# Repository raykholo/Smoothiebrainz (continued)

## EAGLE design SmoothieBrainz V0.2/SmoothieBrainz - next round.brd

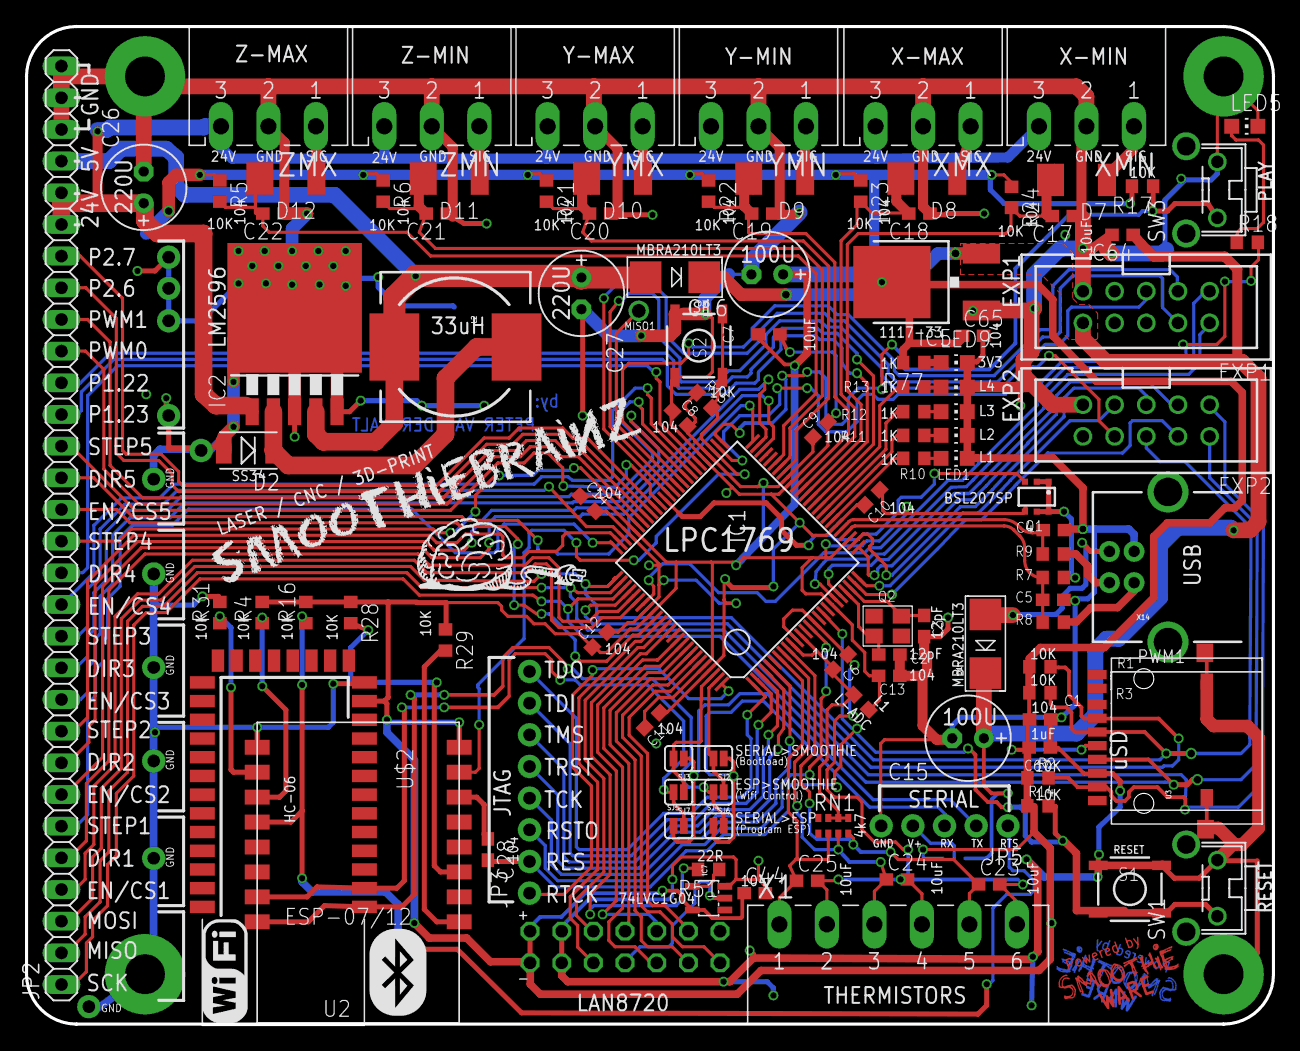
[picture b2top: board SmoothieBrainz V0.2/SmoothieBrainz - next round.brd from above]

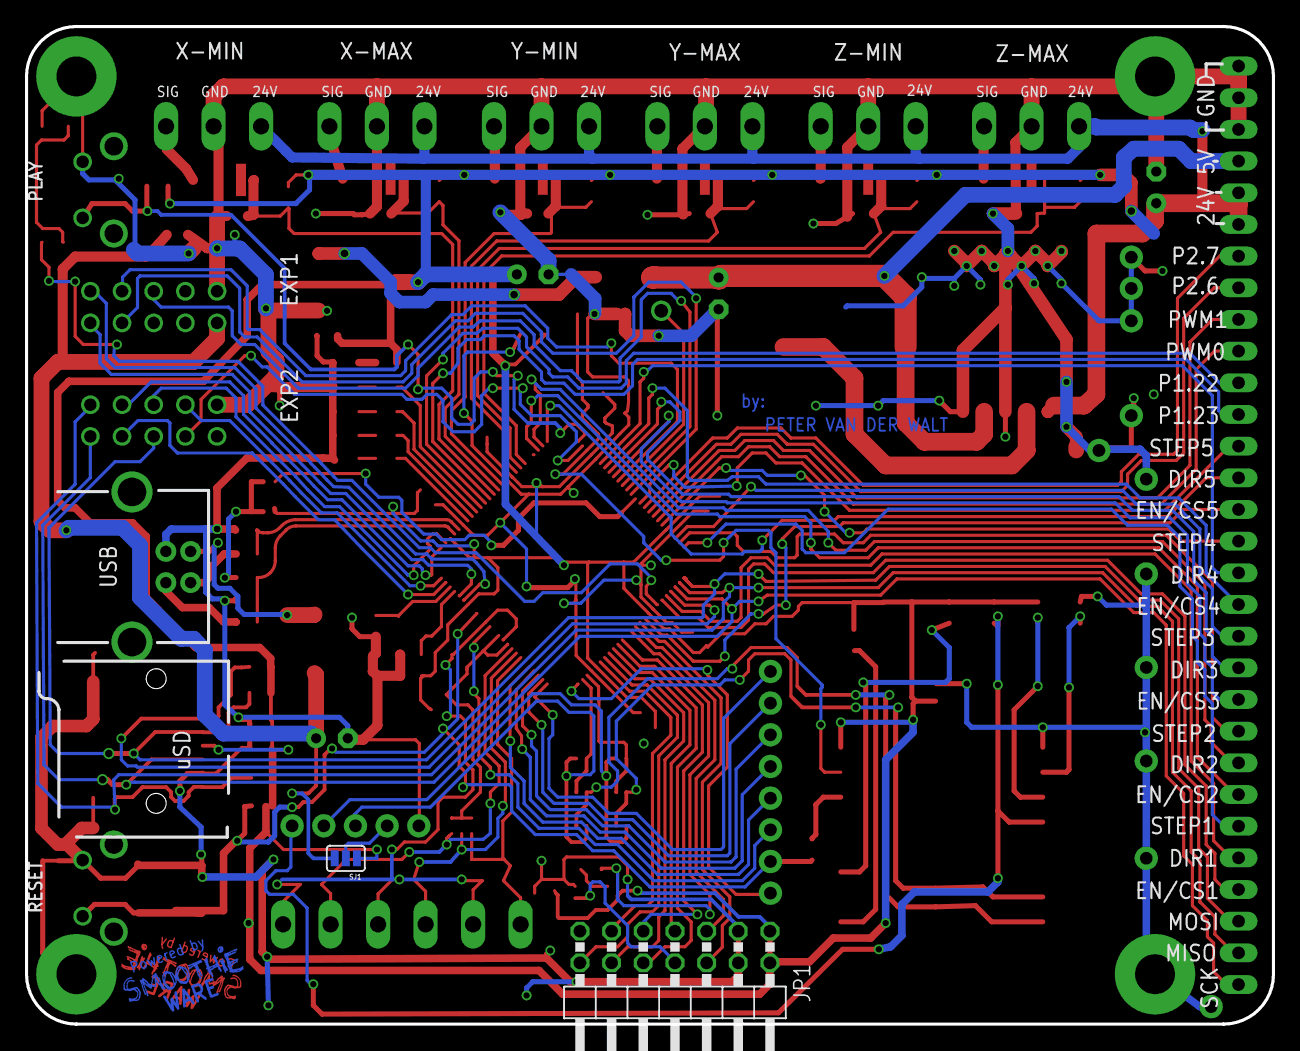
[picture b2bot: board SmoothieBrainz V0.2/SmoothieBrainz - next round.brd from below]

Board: 2 copper layers, 100.0 x 80.0 mm, 122 parts (2 on the bottom side), 112 nets.

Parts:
C1, C6, C8, C9, C10, C11, C12, C13, C14, C28, C44, C65: .1uF; C0603
C2, C3: 12pF; C0603
C4, C5: 18pF; C0603
C7, C23, C24, C25, C64: 10uF; C0603
C15, C16: E2,5-7
C17, C18, C19, C20, C21, C22: 104; C0603
C26, C27: 220u; E2,5-7
C67: 1uF; C0603
D1, D3: MBRA210LT3; SMADIODE
D2: DO-214AC
D7, D8, D9, D10, D11, D12: SOD87
EXP1, EXP2: 2510-; PAK100/2500-10
IC1: LPC1769; LQFP100
IC2: TO263-5
IC5: LD117ADT33TR; DPACK
IC7: SOT23-5
JP1: 2X07/90
JP2: 1X30
JP3: 1X08_NO_SILK
JP5: 1X05_NO_SILK
JP6, JP7, JP8, JP9, JP10, JP11, JP12, JP13, JP14, JP15, JP16: 1X01NS-KIT
L1: 0603
L2: 33uH; CDRH125
LED1, LED2, LED3, LED4, LED5, LED9: CHIP-LED0805
Q1: BSL207SP; SC74_INFINEON
Q2: 12MHz; CRYSTAL_3.2X2.5
R1, R2, R3, R14, R15, R17: 10K; R0603
R4, R16, R28, R29, R31: 1K; R0603
R5, R6, R21, R22, R23, R24: 10k; R0603
R7: 1.5K; R0603
R8, R9: 33R; R0603
R10, R11, R12, R13, R18, R77: 1k; R0603
R51: 22R; R0603
RN1: 4.7K; 0603-ARV
S1, S2: TACTILE_SWITCH_SMD
SJ1: SJ_3
SJ2, SJ3, SJ4, SJ5, SJ6, SJ7: SOLDERJUMPERNC; SJ_2S
SW1, SW3: SW_TACT_4P_B; SW_TACT_STANDARD_RIGHT_ANGLE
U2: HC_05; BLUETOOTH_SMD
U3: USD-SOCKETUSD; USD-SOCKET-PP
U$2: ESP8266_ESP-12; ESP8266-ESP12
X1: MC1.5/6-G-3.81
X14: USBPTH; USB-B-PTH
XMN: MC1.5/3-G-3.81
XMX: MC1.5/3-G-3.81
YMN: MC1.5/3-G-3.81
YMX: MC1.5/3-G-3.81
ZMN: MC1.5/3-G-3.81
ZMX: MC1.5/3-G-3.81

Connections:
2: R4.1, U$2.3
3.3V: C1.2, C7.1, C8.2, C9.2, C10.2, C11.2, C12.2, C13.2, C14.2, C16.+, C44.1, C65.1, C67.2, IC1.19, IC1.28, IC1.42, IC1.54, IC1.71, IC1.84, IC1.96, IC5.4, IC7.5, JP1.1, JP1.2, L1.2, Q1.4, R1.2, R2.2, R3.2, R4.2, R5.1, R6.1, R14.2, R15.2, R16.2, R17.2, R21.1, R22.1, R23.1, R24.1, R28.1, R29.1, R77.2, SJ1.1, U2.12, U3.4, U$2.16
5V: C15.+, C64.1, D1.C, D3.C, EXP1.10, IC5.3, SJ1.3
5VREG: C27.+, D3.A, IC2.4, JP2.27, L2.2
12: C28.1, U$2.14
15: R31.1, U$2.2
24V: C26.+, IC2.1, JP2.25, JP2.26, XMN.3, XMX.3, YMN.3, YMX.3, ZMN.3, ZMX.3
AGND: C6.2, C23.2, C24.2, C25.2, IC1.11, IC1.15, X1.2, X1.4, X1.6
AVCC: C6.1, IC1.10, IC1.12, L1.1, RN1.1, RN1.2, RN1.3
BUZZER-RRD: EXP1.1, IC1.20
DIR1: IC1.80, JP2.5
DIR2: IC1.49, JP2.8
DIR3: IC1.58, JP2.11
DIR4: IC1.56, JP2.14
DIR5: IC1.50, JP2.17
EN1: IC1.81, JP2.4
EN2: IC1.48, JP2.7
EN3: IC1.59, JP2.10
EN4: IC1.57, JP2.13
EN5: IC1.85, JP2.16
ENET_CRS: IC1.92, JP1.7
ENET_MDC: IC1.87, JP1.5
ENET_MDIO: IC1.86, JP1.6
ENET_REF_CLK: IC1.88, R51.2
ENET_RXD0: IC1.91, JP1.10
ENET_RXD1: IC1.90, JP1.9
ENET_TXD0: IC1.95, JP1.11
ENET_TXD1: IC1.94, JP1.14
ENET_TX_EN: IC1.93, JP1.12
ESPRX: SJ5.2, SJ7.2, U2.2, U$2.7
ESPTX: SJ4.2, SJ6.2, U2.1, U$2.8
GND: C1.1, C2.2, C3.2, C4.1, C5.1, C7.2, C8.1, C9.1, C10.1, C11.1, C12.1, C13.1, C14.1, C15.-, C16.-, C17.1, C18.1, C19.1, C20.1, C21.1, C22.1, C26.-, C27.-, C44.2, C64.2, C65.2, C67.1, D2.2, EXP1.9, EXP2.9, IC1.31, IC1.41, IC1.55, IC1.72, IC1.83, IC1.97, IC2.3, IC2.5, IC2.6, IC5.1, IC7.3, JP1.3, JP1.4, JP2.28, JP2.29, JP2.30, JP5.5, JP6.1, JP7.1, JP8.1, JP9.1, JP10.1, JP11.1, JP12.1, JP13.1, JP14.1, JP15.1, JP16.1, LED1.C, LED2.C, LED3.C, LED4.C, LED5.C, LED9.C, R31.2, S1.3, S1.4, S2.3, S2.4, SW1.2, SW3.2, U2.13, U3.6, U3.CDNC1, U3.CDNC2, U3.GND1, U3.GND2, U$2.1, X14.GND, XMN.2, XMX.2, YMN.2, YMX.2, ZMN.2, ZMX.2
ISP_BOOT: IC1.53, R15.1, S2.1, S2.2, U$2.15
JTAG-RTCK: IC1.100, JP3.1
JTAG-TCK: IC1.5, JP3.4
JTAG-TDI: IC1.2, JP3.7
JTAG-TDO: IC1.1, JP3.8
JTAG-TMS: IC1.3, JP3.6
JTAG-TRST: IC1.4, JP3.5
LED1: IC1.32, R10.2
LED2: IC1.33, R11.2
LED3: IC1.34, R12.2
LED4: IC1.35, R13.2
MOSI1: EXP1.3, IC1.60
unnamed: C2.1, IC1.22, Q2.2
unnamed: C3.1, IC1.23, Q2.1
unnamed: LED5.A, R18.1
unnamed: D7.1, XMN.1
unnamed: D8.1, XMX.1
unnamed: D2.1, IC2.2, L2.1
unnamed: D9.1, YMN.1
unnamed: D10.1, YMX.1
unnamed: D11.1, ZMN.1
unnamed: D12.1, ZMX.1
unnamed: R28.2, U$2.11
unnamed: JP5.4, SJ1.2
unnamed: Q1.1, Q1.2, Q1.5, Q1.6, R7.2
unnamed: R8.1, X14.D+
unnamed: R9.1, X14.D-
unnamed: IC7.2, JP1.8
unnamed: IC7.4, R51.1
unnamed: LED9.A, R77.1
unnamed: LED4.A, R13.1
unnamed: LED3.A, R12.1
unnamed: LED2.A, R11.1
unnamed: LED1.A, R10.1
P1_22-3RD-SMALL-FET: IC1.36, JP2.20
P1_23-3RD-LARGE-FET: IC1.37, JP2.19
P1_30_CLICK-ON-RRD: EXP1.2, IC1.21
P2.6_FAN_FET: IC1.67, JP2.23
P2.7_HOTEND_FET: IC1.66, JP2.24
P2.9: IC1.64, Q1.3
PLAY: IC1.51, R17.1, SW3.1
PLAY_LED: IC1.82, R18.2
PWM0_PSU_OUT: IC1.69, JP2.21
PWM1_BED_HEATER: IC1.68, JP2.22
RESET: C28.2, IC1.17, JP3.2, R14.1, S1.1, S1.2, SW1.1
RESET1: R29.2, U$2.9
RSTOUT: IC1.14, JP3.3
RTS: JP5.1, R16.1, U$2.4
RX_0: IC1.99, SJ2.2, SJ6.1
RX_FT: JP5.3, SJ2.1, SJ4.1
SCK1: EXP1.5, IC1.62
SD-CD-ON-RRD: EXP2.7, IC1.25
SD-CS-ON-RRD: EXP2.4, IC1.24
SD_CD/KILL-ON-RRD: EXP2.8, IC1.52
SD_CS: IC1.79, R1.1, U3.2
SD_IRQ-ENC-A-ON-RRD: EXP2.5, IC1.27
SD_MISO: EXP2.1, IC1.77, JP2.2, R2.1, U3.7
SD_MOSI: EXP2.6, IC1.76, JP2.3, R3.1, U3.3
SD_SCK: EXP2.2, IC1.78, JP2.1, U3.5
SD_WP-ENC-B-ON-RRD: EXP2.3, IC1.26
SSEL1: EXP1.4, IC1.63
STP1: IC1.75, JP2.6
STP2: IC1.74, JP2.9
STP3: IC1.73, JP2.12
STP4: IC1.70, JP2.15
STP5: IC1.65, JP2.18
TH1_HOTEND: C23.1, IC1.9, RN1.8, X1.5
TH2_BED: C24.1, IC1.8, RN1.7, X1.3
TH3: C25.1, IC1.7, RN1.6, X1.1
TX_0: IC1.98, SJ3.2, SJ7.1
TX_FT: JP5.2, SJ3.1, SJ5.1
USB_D+: C5.2, IC1.29, R7.1, R8.2
USB_D-: C4.2, IC1.30, R9.2
VUSB: D1.A, X14.VBUS
X_MAX: C18.2, D8.2, IC1.39, R23.2
X_MIN: C17.2, D7.2, IC1.38, R24.2
Y_MAX: C20.2, D10.2, IC1.43, R21.2
Y_MIN: C19.2, D9.2, IC1.40, R22.2
Z_MAX: C22.2, D12.2, IC1.45, R5.2
Z_MIN: C21.2, D11.2, IC1.44, R6.2

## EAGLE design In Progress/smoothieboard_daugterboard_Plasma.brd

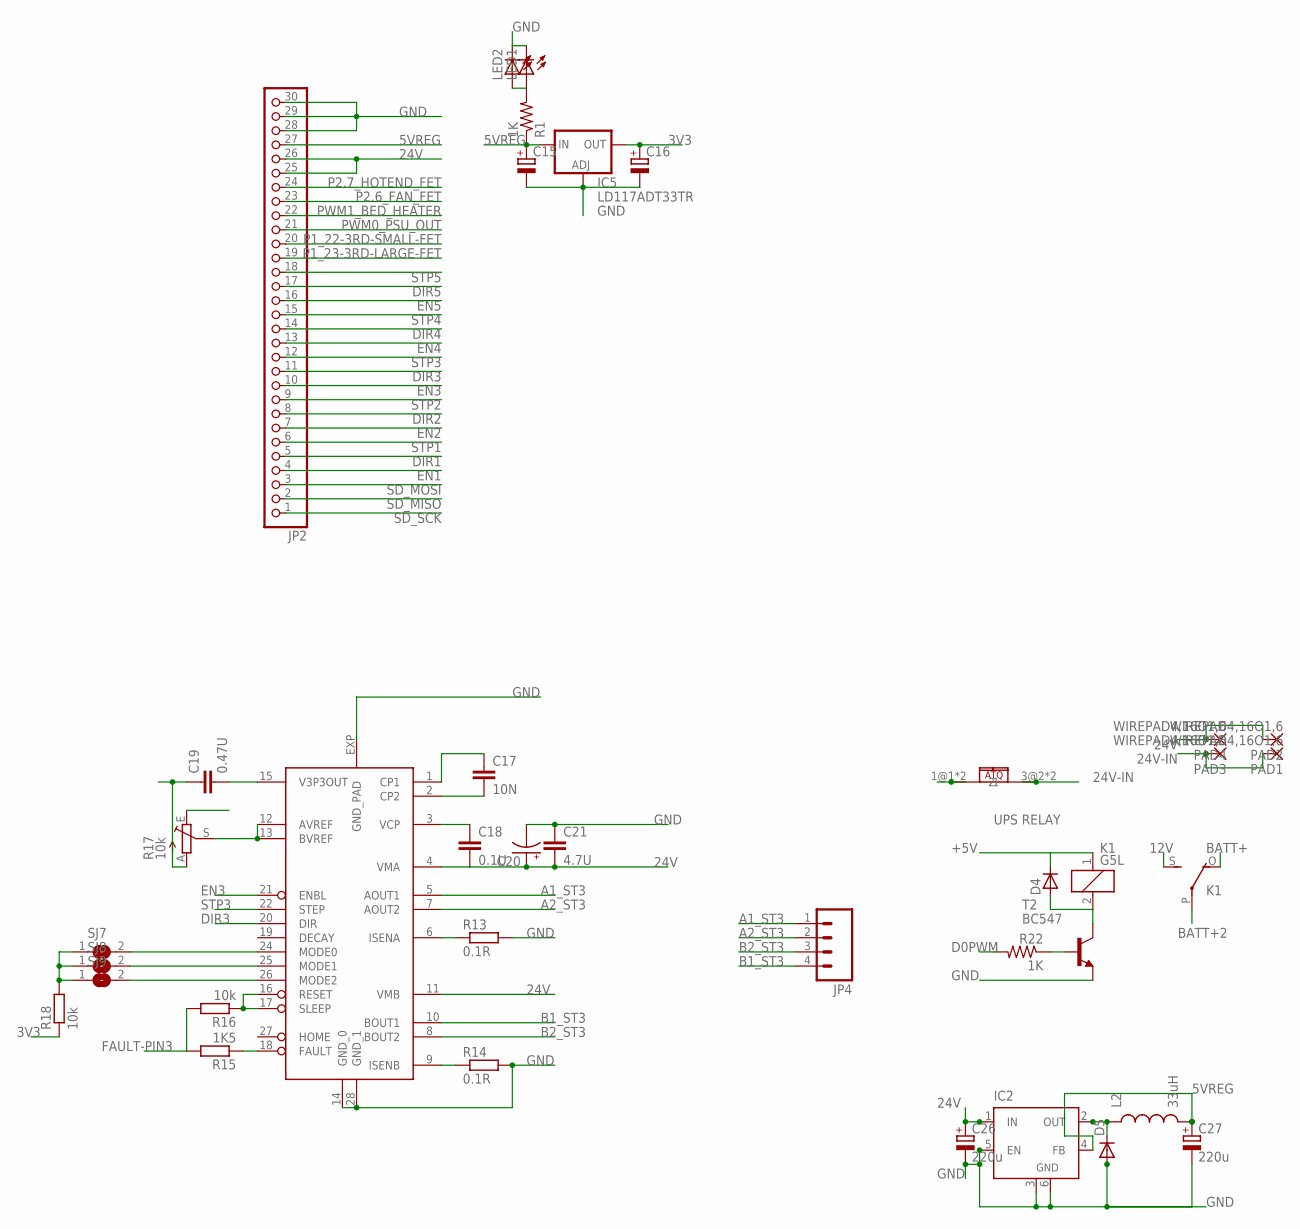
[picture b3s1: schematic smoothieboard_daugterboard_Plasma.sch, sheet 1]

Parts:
C15, C16: CPOL-EUB/3528-21R; B/3528-21R
C17: 10N; 1206
C18: 0.1U; 1206
C19: 0.47U; 0805
C20: CPOL-USE2.5-7; E2,5-7
C21: 4.7U; 1206
C26, C27: 220u; PANASONIC_E
D4: D-MLL-41; MELF-MLL41
D5: DIODE-DO-214AC; DO-214AC
IC2: LM2596S; TO263-5
IC5: LD117ADT33TR; DPACK
JP2: PINHD-1X30; 1X30
JP4: M04SCREW; SCREWTERMINAL-3.5MM-4
K1: G5L; G5LE
L2: 33uH; CDRH125
LED1: LEDCHIPLED_1206; CHIPLED_1206
LED2: LED3MM
PAD1, PAD2, PAD3, PAD4: WIREPAD4,16O1,6; 4,16O1,6
R1, R22: 1K; M1206
R13, R14: 0.1R; R1206
R15: 1K5; R0805
R16: 10k; R0805
R17: 10k; S64W
R18: 10k; R1206
SJ7, SJ8, SJ9: SJ
T2: BC547; TO92
U$3: DRV8825PWP; TSSOP-28
U$7: CQ-121; CQ121

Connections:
3V3: C16.+, IC5.4 (OUT), R17.E, R18.1
5VREG: C15.+, C27.+, IC2.4 (FB), IC5.3 (IN), JP2.27, L2.2, R1.1
12V: K1.S
24V: C18.2, C20.+, C21.2, C26.+, IC2.1 (IN), JP2.25, JP2.26, PAD2.1, PAD4.1, U$3.4 (VMA), U$3.11 (VMB)
24V-DC: U$7.1@1 (1), U$7.2@1 (1)
24V-IN: PAD1.1, PAD3.1, U$7.3@2 (2), U$7.4@2 (2)
+5V: D4.1 (C), K1.1
A1_ST3: JP4.1, U$3.5 (AOUT1)
A2_ST3: JP4.2, U$3.7 (AOUT2)
B1_ST3: JP4.4, U$3.10 (BOUT1)
B2_ST3: JP4.3, U$3.8 (BOUT2)
BATT+: K1.O
BATT+2: K1.P
CP5: C17.2, U$3.2 (CP2)
CP6: C17.1, U$3.1 (CP1)
D0PWM: R22.2
DIR1: JP2.5
DIR2: JP2.8
DIR3: JP2.11, U$3.20 (DIR)
DIR4: JP2.14
DIR5: JP2.17
EN1: JP2.4
EN2: JP2.7
EN3: JP2.10, U$3.21 (ENBL)
EN4: JP2.13
EN5: JP2.16
FAULT3: R15.1, U$3.18 (FAULT)
FAULT-PIN3: R15.2, R16.2
GND: C15.-, C16.-, C19.1, C20.-, C21.1, C26.-, C27.-, D5.2 (A), IC2.3 (GND), IC2.5 (EN), IC2.6 (GND), IC5.1 (ADJ), JP2.28, JP2.29, JP2.30, LED1.C, LED2.K (C), R13.2, R14.2, R17.A, T2.1 (E), U$3.14 (GND_0), U$3.28 (GND_1), U$3.EXP (GND_PAD)
MSPULLUP2: R18.2, SJ7.1, SJ7.2, SJ8.1, SJ8.2, SJ9.1, SJ9.2, U$3.24 (MODE0), U$3.25 (MODE1), U$3.26 (MODE2)
unnamed: LED1.A, LED2.A, R1.2
unnamed: R17.S, U$3.12 (AVREF), U$3.13 (BVREF)
unnamed: D4.2 (A), K1.2, T2.3 (C)
unnamed: R22.1, T2.2 (B)
unnamed: D5.1 (C), IC2.2 (OUT), L2.1
P1_22-3RD-SMALL-FET: JP2.20
P1_23-3RD-LARGE-FET: JP2.19
P2.6_FAN_FET: JP2.23
P2.7_HOTEND_FET: JP2.24
PWM0_PSU_OUT: JP2.21
PWM1_BED_HEATER: JP2.22
SD_MISO: JP2.2
SD_MOSI: JP2.3
SD_SCK: JP2.1
SENA2: R13.1, U$3.6 (ISENA)
SENB2: R14.1, U$3.9 (ISENB)
SLEEP2: R16.1, U$3.16 (RESET), U$3.17 (SLEEP)
STP1: JP2.6
STP2: JP2.9
STP3: JP2.12, U$3.22 (STEP)
STP4: JP2.15
STP5: JP2.18
V3VP3: C19.2, U$3.15 (V3P3OUT)
VCP2: C18.1, U$3.3 (VCP)

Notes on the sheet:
UPS RELAY

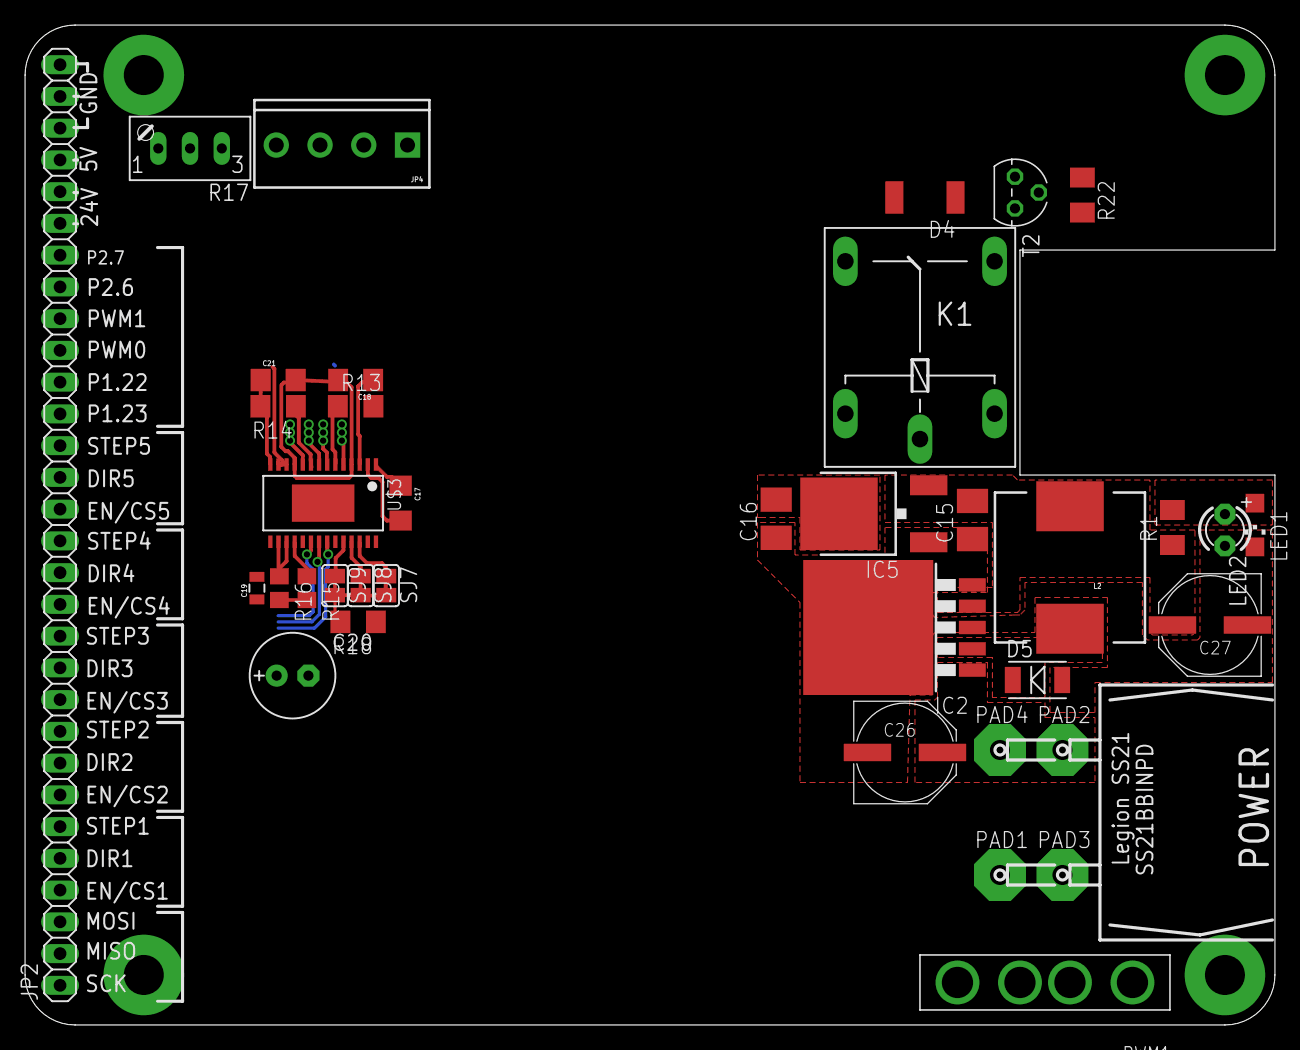
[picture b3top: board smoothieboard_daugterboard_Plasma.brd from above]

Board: 2 copper layers, 100.0 x 80.0 mm, 37 parts (0 on the bottom side), 29 nets.

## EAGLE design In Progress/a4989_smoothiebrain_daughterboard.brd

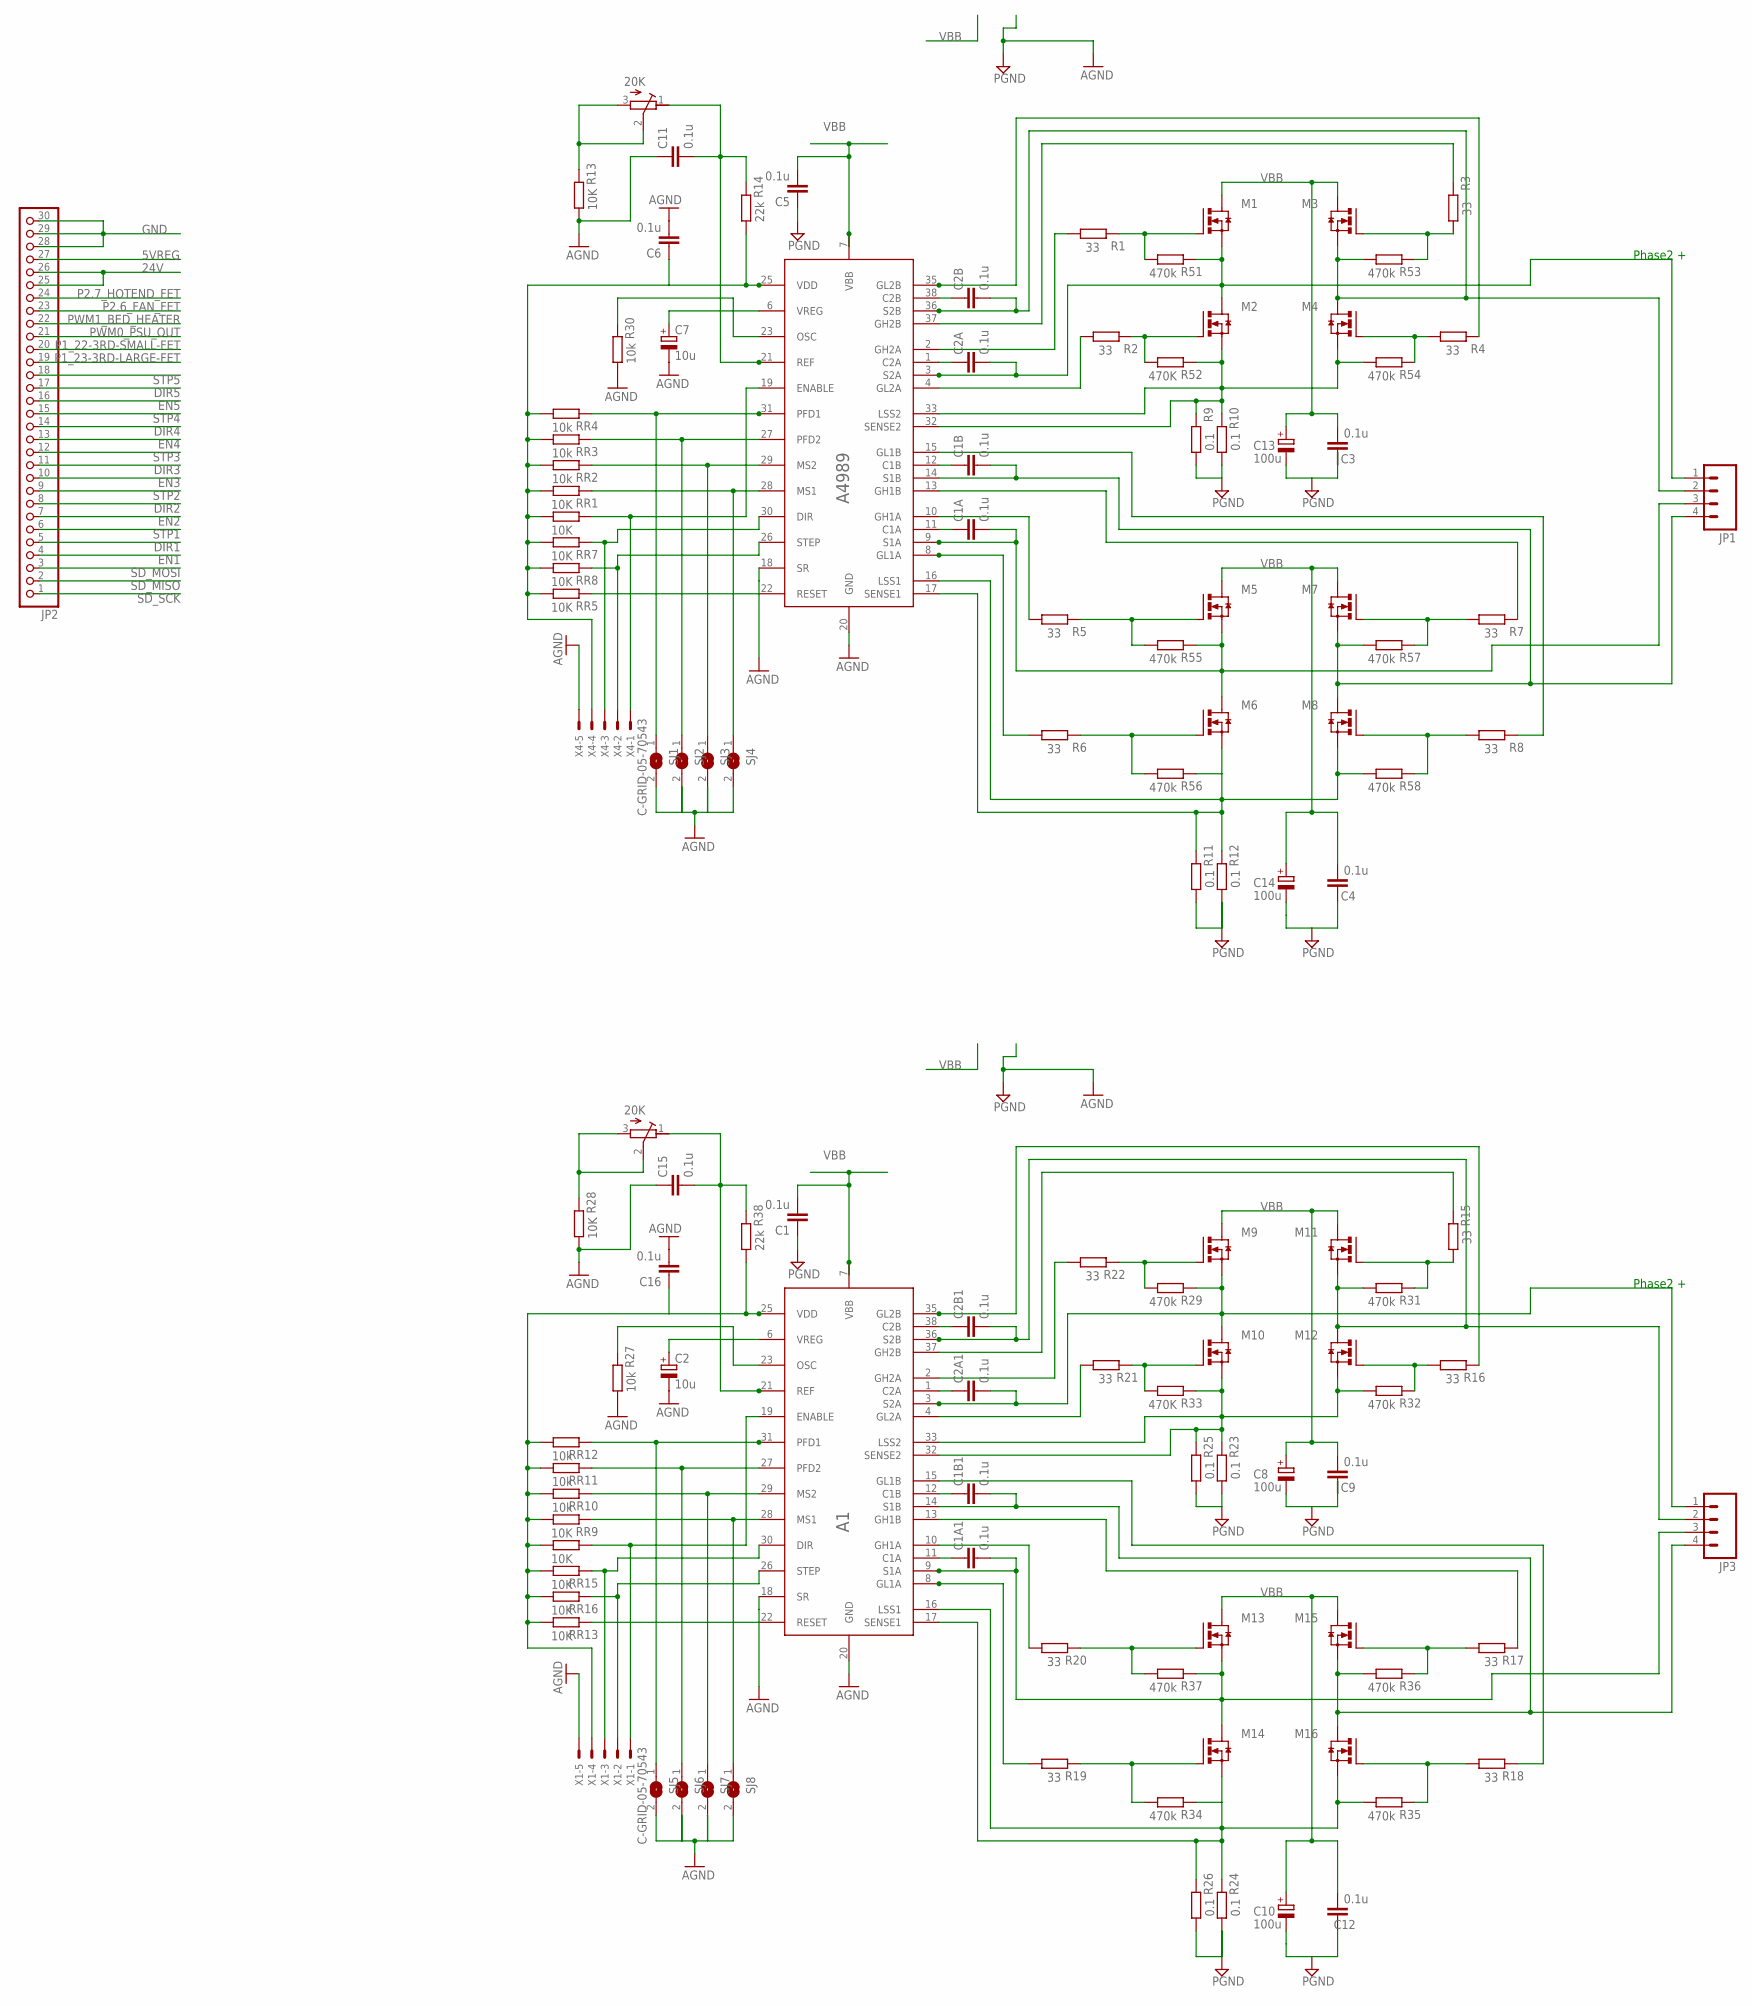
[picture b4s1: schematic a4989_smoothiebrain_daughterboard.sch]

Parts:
A1, A4989: A4989; TSSOP39
C1, C1A, C1A1, C1B, C1B1, C2A, C2A1, C2B, C2B1, C3, C4, C5, C6, C9, C11, C12, C15, C16: 0.1u; C0603
C2, C7: 10u; 153CLV-0605
C8, C10, C13, C14: 100u; E5-10,5
JP1, JP3: M04SCREW; SCREWTERMINAL-3.5MM-4
JP2: PINHD-1X30; 1X30
M1, M2, M3, M4, M5, M6, M7, M8, M9, M10, M11, M12, M13, M14, M15, M16: IRLR024N; TO252
R1, R2, R3, R4, R5, R6, R7, R8, R15, R16, R17, R18, R19, R20, R21, R22: 33; R0603
R9, R10, R11, R12, R23, R24, R25, R26: 0.1; R2512
R13, R28: 10K; R0603
R14, R38: 22k; R0603
R27, R30: 10k; R0603
R29, R31, R32, R34, R35, R36, R37, R51, R53, R54, R55, R56, R57, R58: 470k; R0603
R33, R52: 470K; R0603
RR1, RR5, RR6, RR7, RR8, RR9, RR13, RR14, RR15, RR16: 10K; R0603
RR2, RR3, RR4, RR10, RR11, RR12: 10k; R0603
SJ1, SJ2, SJ3, SJ4, SJ5, SJ6, SJ7, SJ8: SJ
U$1, U$2: 20K; BOURNS_3266W
X1, X4: C-GRID-05-70543; 70543-05

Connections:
5VREG: A4989.25 (VDD), C6.1, JP2.27, R14.2, RR1.2, RR2.2, RR3.2, RR4.2, RR5.2, RR6.2, RR7.2, RR8.2, X4.4
5VREG1: A1.25 (VDD), C16.1, R38.2, RR9.2, RR10.2, RR11.2, RR12.2, RR13.2, RR14.2, RR15.2, RR16.2, X1.4
24V: JP2.25, JP2.26
DIR1: A4989.30 (DIR), JP2.5, RR7.1, X4.3
DIR2: JP2.8
DIR3: JP2.11
DIR4: JP2.14
DIR5: JP2.17
DIR6: A1.30 (DIR), RR15.1, X1.3
EN1: A4989.19 (ENABLE), JP2.4, RR6.1, X4.1
EN2: JP2.7
EN3: JP2.10
EN4: JP2.13
EN5: JP2.16
EN6: A1.19 (ENABLE), RR14.1, X1.1
GH1A: A4989.10 (GH1A), R5.2
GH1A1: A1.10 (GH1A), R20.2
GH1B: A4989.13 (GH1B), R7.1
GH1B1: A1.13 (GH1B), R17.1
GH2A: A4989.2 (GH2A), R1.2
GH2A1: A1.2 (GH2A), R22.2
GH2B: A4989.37 (GH2B), R3.1
GH2B1: A1.37 (GH2B), R15.1
GL1A: A4989.8 (GL1A), R6.2
GL1A1: A1.8 (GL1A), R19.2
GL1B: A4989.15 (GL1B), R8.1
GL1B1: A1.15 (GL1B), R18.1
GL2A: A4989.4 (GL2A), R2.2
GL2A1: A1.4 (GL2A), R21.2
GL2B: A4989.35 (GL2B), R4.1
GL2B1: A1.35 (GL2B), R16.1
GND: A1.18 (SR), A1.20 (GND), A4989.18 (SR), A4989.20 (GND), C1.1, C2.-, C3.1, C4.1, C5.1, C6.2, C7.-, C8.-, C9.1, C10.-, C11.1, C12.1, C13.-, C14.-, C15.1, C16.2, JP2.28, JP2.29, JP2.30, R9.2, R10.2, R11.2, R12.2, R13.2, R23.2, R24.2, R25.2, R26.2, R27.2, R28.2, R30.2, SJ1.2, SJ2.2, SJ3.2, SJ4.2, SJ5.2, SJ6.2, SJ7.2, SJ8.2, X1.5, X4.5
LSS1: A4989.16 (LSS1), A4989.17 (SENSE1), M6.2 (S), M8.2 (S), R11.1, R12.1, R56.1, R58.2
LSS2: A4989.32 (SENSE2), A4989.33 (LSS2), M2.2 (S), M4.2 (S), R9.1, R10.1, R52.1, R54.2
LSS3: A1.32 (SENSE2), A1.33 (LSS2), M10.2 (S), M12.2 (S), R23.1, R25.1, R32.2, R33.1
LSS4: A1.16 (LSS1), A1.17 (SENSE1), M14.2 (S), M16.2 (S), R24.1, R26.1, R34.1, R35.2
MS1: A4989.28 (MS1), RR1.1, SJ4.1
MS2: A4989.29 (MS2), RR2.1, SJ3.1
MS3: A1.29 (MS2), RR10.1, SJ7.1
MS4: A1.28 (MS1), RR9.1, SJ8.1
unnamed: M10.1 (G), R21.1, R33.2
unnamed: M9.1 (G), R22.1, R29.2
unnamed: M11.1 (G), R15.2, R31.1
unnamed: M12.1 (G), R16.2, R32.1
unnamed: M14.1 (G), R19.1, R34.2
unnamed: M2.1 (G), R2.1, R52.2
unnamed: M1.1 (G), R1.1, R51.2
unnamed: M3.1 (G), R3.2, R53.1
unnamed: M4.1 (G), R4.2, R54.1
unnamed: M6.1 (G), R6.1, R56.2
unnamed: M5.1 (G), R5.1, R55.2
unnamed: M7.1 (G), R7.2, R57.1
unnamed: M8.1 (G), R8.2, R58.1
unnamed: M13.1 (G), R20.1, R37.2
unnamed: M15.1 (G), R17.2, R36.1
unnamed: R13.1, U$1.2 (S), U$1.3 (E)
unnamed: M16.1 (G), R18.2, R35.1
unnamed: A4989.22 (RESET), RR5.1
unnamed: A1.12 (C1B), C1B1.1
unnamed: A1.11 (C1A), C1A1.1
unnamed: A1.1 (C2A), C2A1.1
unnamed: A1.38 (C2B), C2B1.1
unnamed: R28.1, U$2.2 (S), U$2.3 (E)
unnamed: A1.22 (RESET), RR13.1
unnamed: A4989.12 (C1B), C1B.1
unnamed: A4989.11 (C1A), C1A.1
unnamed: A4989.1 (C2A), C2A.1
unnamed: A4989.38 (C2B), C2B.1
OSC: A4989.23 (OSC), R30.1
OSC1: A1.23 (OSC), R27.1
P1+: A4989.9 (S1A), C1A.2, JP1.3, M5.2 (S), M6.3 (D), R55.1
P1+1: A1.9 (S1A), C1A1.2, JP3.3, M13.2 (S), M14.3 (D), R37.1
P1-: A4989.14 (S1B), C1B.2, JP1.4, M7.2 (S), M8.3 (D), R57.2
P1-1: A1.14 (S1B), C1B1.2, JP3.4, M15.2 (S), M16.3 (D), R36.2
P1_22-3RD-SMALL-FET: JP2.20
P1_23-3RD-LARGE-FET: JP2.19
P2+: A4989.3 (S2A), C2A.2, JP1.1, M1.2 (S), M2.3 (D), R51.1
P2+1: A1.3 (S2A), C2A1.2, JP3.1, M9.2 (S), M10.3 (D), R29.1
P2-: A4989.36 (S2B), C2B.2, JP1.2, M3.2 (S), M4.3 (D), R53.2
P2-1: A1.36 (S2B), C2B1.2, JP3.2, M11.2 (S), M12.3 (D), R31.2
P2.6_FAN_FET: JP2.23
P2.7_HOTEND_FET: JP2.24
PFD1: A4989.31 (PFD1), RR4.1, SJ1.1
PFD2: A4989.27 (PFD2), RR3.1, SJ2.1
PFD3: A1.31 (PFD1), RR12.1, SJ5.1
PFD4: A1.27 (PFD2), RR11.1, SJ6.1
PWM0_PSU_OUT: JP2.21
PWM1_BED_HEATER: JP2.22
REF: A4989.21 (REF), C11.2, R14.1, U$1.1 (A)
REF1: A1.21 (REF), C15.2, R38.1, U$2.1 (A)
SD_MISO: JP2.2
SD_MOSI: JP2.3
SD_SCK: JP2.1
STP1: A4989.26 (STEP), JP2.6, RR8.1, X4.2
STP2: JP2.9
STP3: JP2.12
STP4: JP2.15
STP5: JP2.18
STP6: A1.26 (STEP), RR16.1, X1.2
VBB: A1.7 (VBB), A4989.7 (VBB), C1.2, C3.2, C4.2, C5.2, C8.+, C9.2, C10.+, C12.2, C13.+, C14.+, M1.3 (D), M3.3 (D), M5.3 (D), M7.3 (D), M9.3 (D), M11.3 (D), M13.3 (D), M15.3 (D)
VREG: A4989.6 (VREG), C7.+
VREG1: A1.6 (VREG), C2.+

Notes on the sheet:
Phase2 +

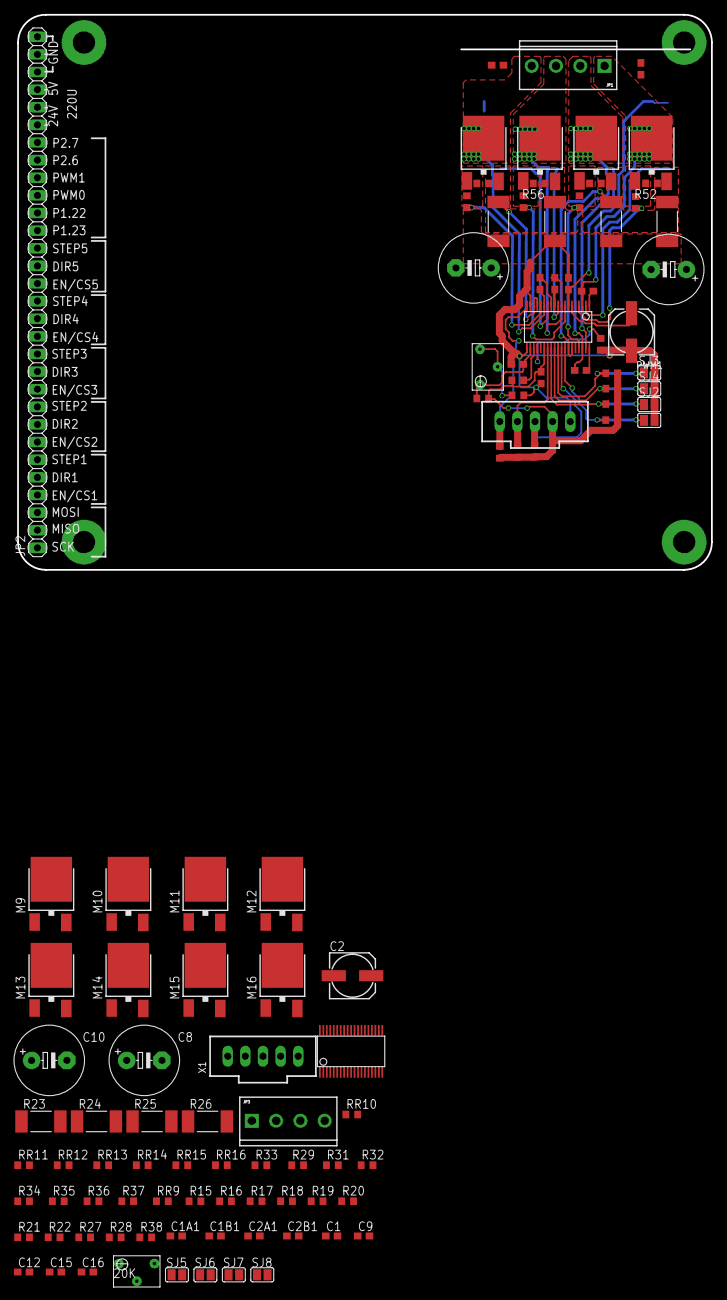
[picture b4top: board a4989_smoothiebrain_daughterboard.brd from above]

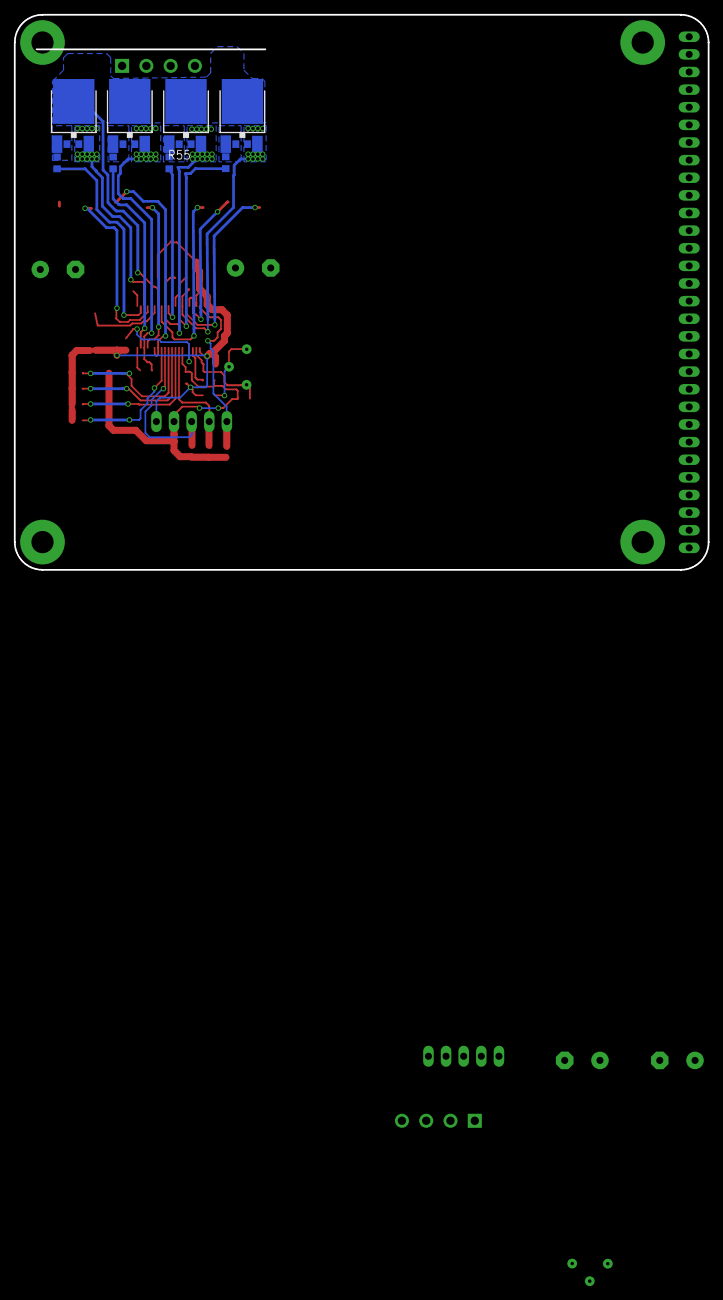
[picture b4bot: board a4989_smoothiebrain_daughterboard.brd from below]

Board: 2 copper layers, 100.0 x 80.0 mm, 119 parts (12 on the bottom side), 81 nets.

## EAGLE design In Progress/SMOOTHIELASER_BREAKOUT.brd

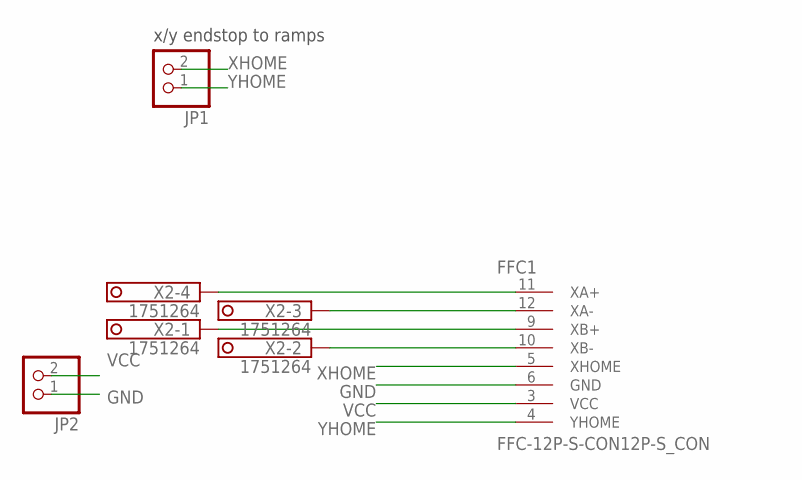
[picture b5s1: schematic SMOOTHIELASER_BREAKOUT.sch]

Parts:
FFC1: FFC-12P-S-CON12P-S_CON; FFC
JP1, JP2: PINHD-1X2; 1X02
X2: 1751264

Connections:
GND: FFC1.6 (GND), JP2.1
unnamed: FFC1.11 (XA+), X2.4
unnamed: FFC1.12 (XA-), X2.3
unnamed: FFC1.10 (XB-), X2.2
unnamed: FFC1.9 (XB+), X2.1
VCC: FFC1.3 (VCC), JP2.2
XHOME: FFC1.5 (XHOME), JP1.2
YHOME: FFC1.4 (YHOME), JP1.1

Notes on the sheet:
x/y endstop to ramps

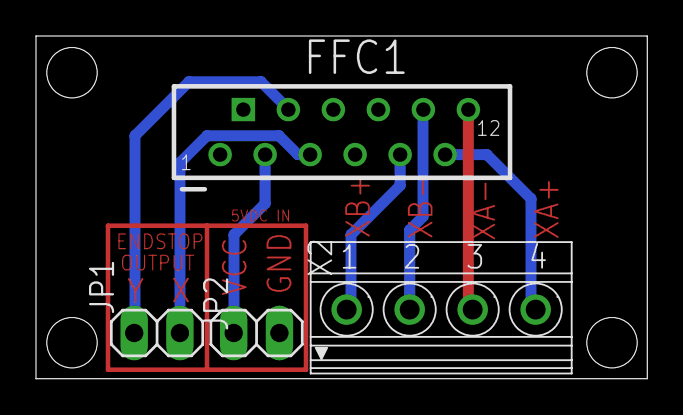
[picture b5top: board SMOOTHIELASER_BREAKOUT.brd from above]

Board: 2 copper layers, 34.0 x 19.0 mm, 4 parts (0 on the bottom side), 8 nets.
